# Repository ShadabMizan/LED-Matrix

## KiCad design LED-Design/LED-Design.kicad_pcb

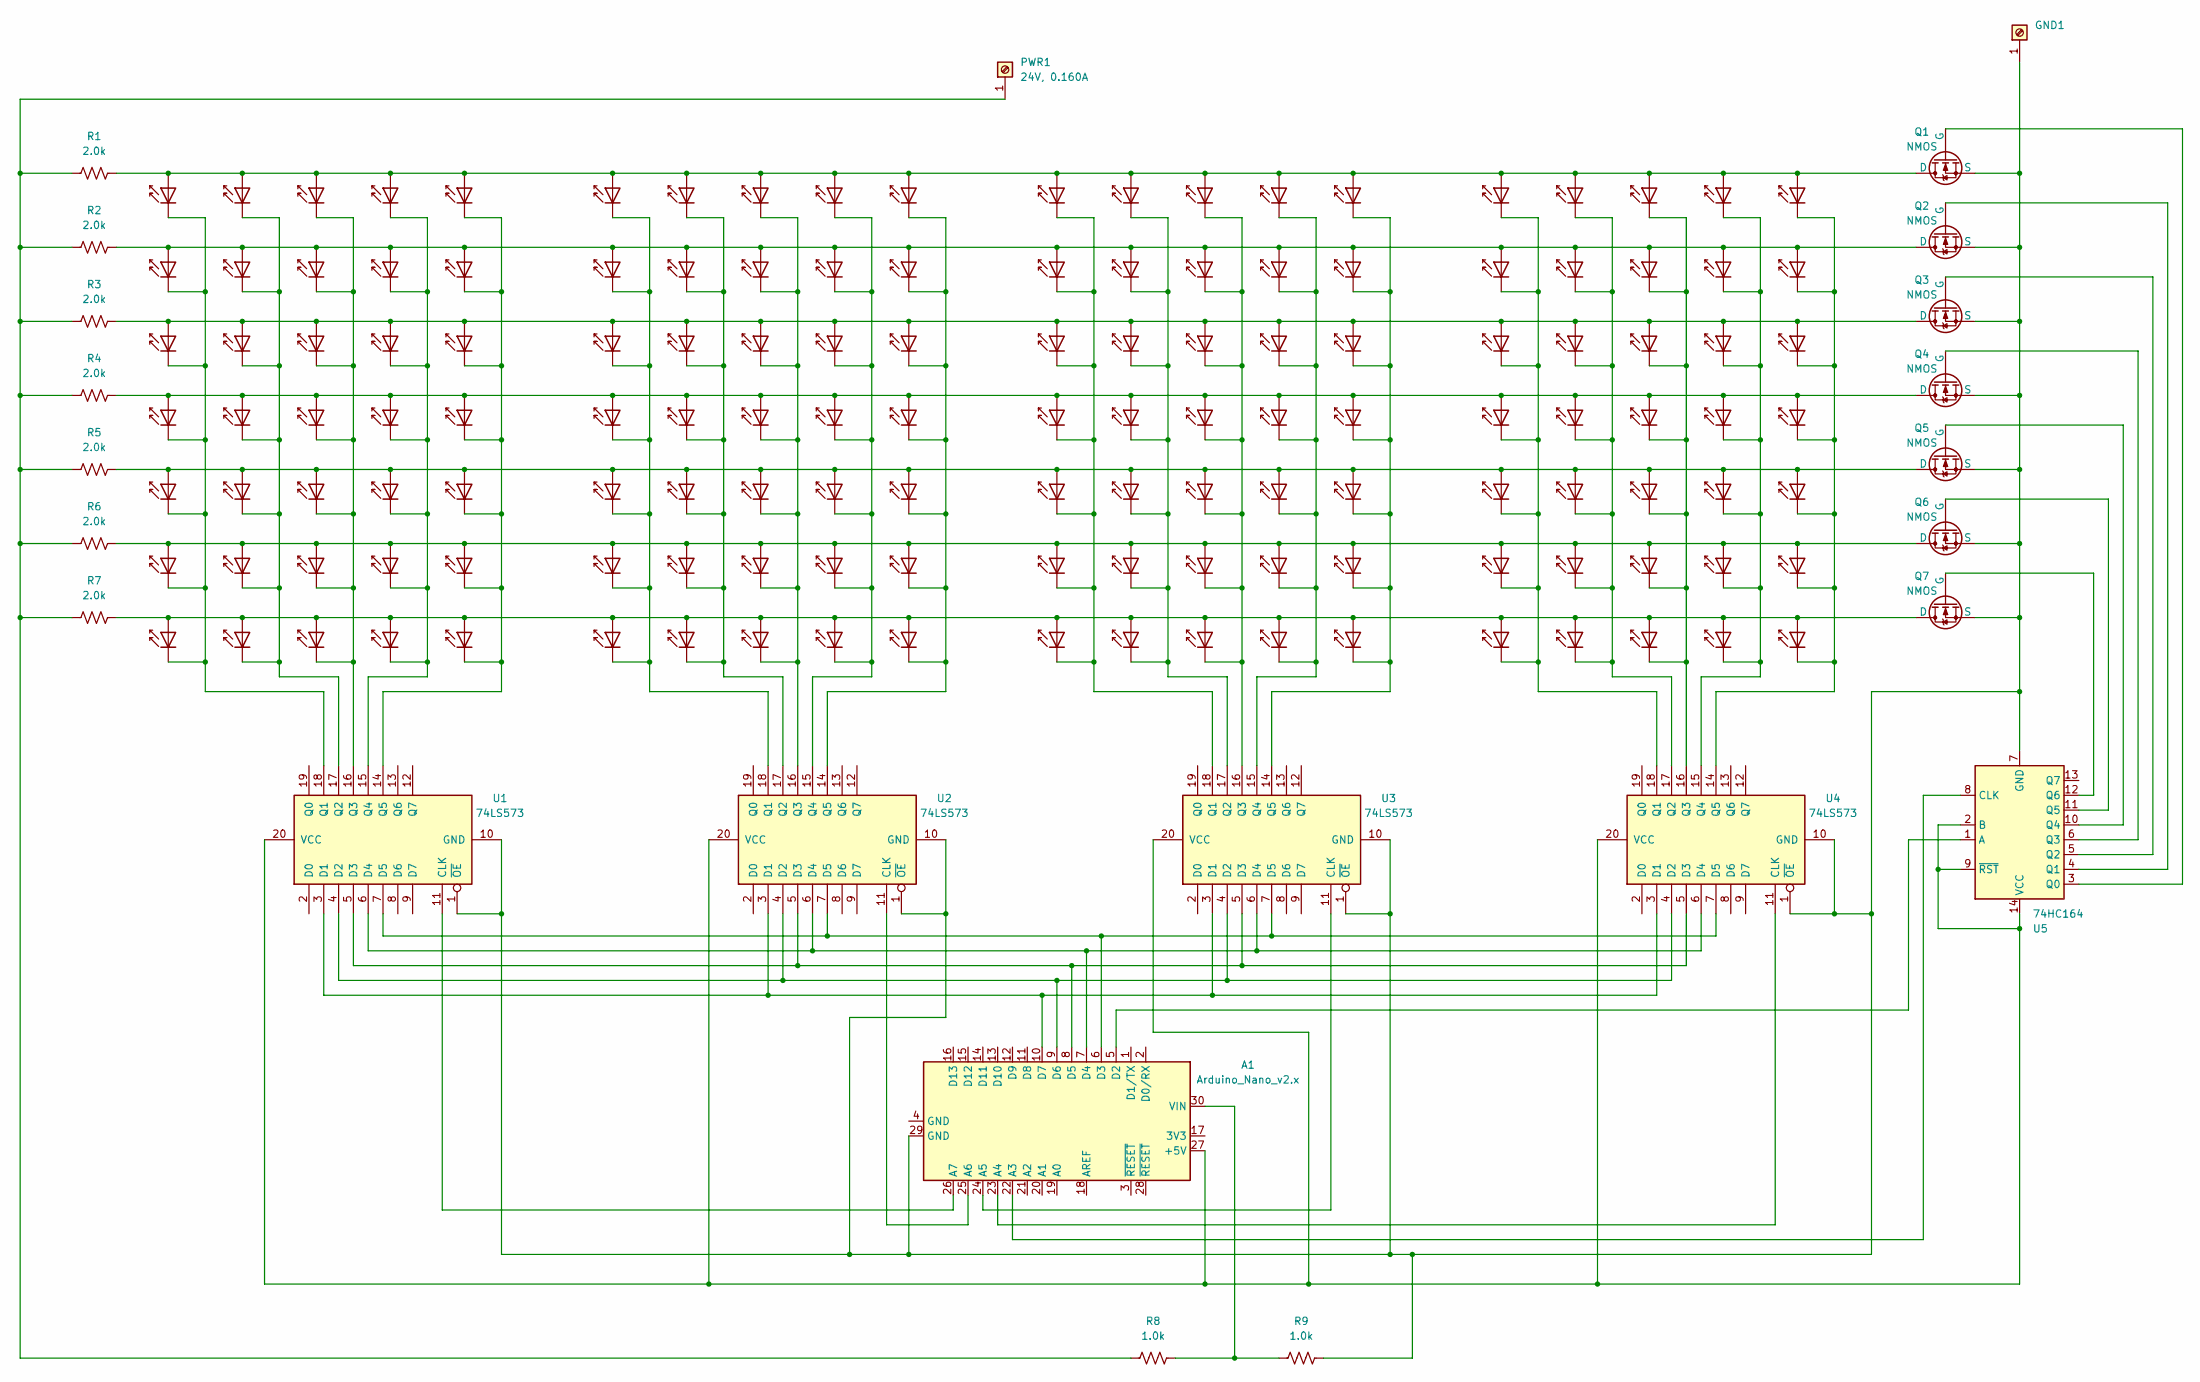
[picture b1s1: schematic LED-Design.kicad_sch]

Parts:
A1: Arduino_Nano_v2.x; Arduino_Nano
D1, D2, D3, D4, D5, D6, D7, D8, D9, D10, D11, D12, D13, D14, D15, D16, D17, D18, D19, D20, D21, D22, D23, D24, D25, D26, D27, D28, D29, D30, D31, D32, D33, D34, D35, D36, D37, D38, D39, D40, D41, D42, D43, D44, D45, D46, D47, D48, D49, D50, D51, D52, D53, D54, D55, D56, D57, D58, D59, D60, D61, D62, D63, D64, D65, D66, D67, D68, D69, D70, D71, D72, D73, D74, D75, D76, D77, D78, D79, D80, D81, D82, D83, D84, D85, D86, D87, D88, D89, D90, D91, D92, D93, D94, D95, D96, D97, D98, D99, D100, D101, D102, D103, D104, D105, D106, D107, D108, D109, D110, D111, D112, D113, D114, D115, D116, D117, D118, D119, D120, D121, D122, D123, D124, D125, D126, D127, D128, D129, D130, D131, D132, D133, D134, D135, D136, D137, D138, D139, D140: IR204A; LED_D3.0mm_IRBlack
GND1: TerminalBlock_MetzConnect_360271_1x01_Horizontal_ScrewM3.0_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
PWR1: 24V, 0.160A; TerminalBlock_MetzConnect_360271_1x01_Horizontal_ScrewM3.0_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
Q1, Q2, Q3, Q4, Q5, Q6, Q7: NMOS; TO-220-3_Vertical
R1, R2, R3, R4, R5, R6, R7: 2.0k; R_LDR_5.2x5.2mm_P3.5mm_Horizontal
R8, R9: 1.0k; R_LDR_5.2x5.2mm_P3.5mm_Horizontal
U1, U2, U3, U4: 74LS573; DIP-20_W7.62mm
U5: 74HC164; DIP-14_W7.62mm

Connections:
unnamed: A1.27 (+5V), U1.20 (VCC), U2.20 (VCC), U3.20 (VCC), U4.20 (VCC), U5.2 (B), U5.9 (~RST), U5.14 (VCC)
unnamed: A1.22 (A3), U5.8 (CLK)
unnamed: A1.23 (A4), U4.11 (CLK)
unnamed: A1.24 (A5), U3.11 (CLK)
unnamed: A1.25 (A6), U2.11 (CLK)
unnamed: A1.26 (A7), U1.11 (CLK)
unnamed: A1.5 (D2), U5.1 (A)
unnamed: A1.6 (D3), U1.7 (D5), U2.7 (D5), U3.7 (D5), U4.7 (D5)
unnamed: A1.7 (D4), U1.6 (D4), U2.6 (D4), U3.6 (D4), U4.6 (D4)
unnamed: A1.8 (D5), U1.5 (D3), U2.5 (D3), U3.5 (D3), U4.5 (D3)
unnamed: A1.9 (D6), U1.4 (D2), U2.4 (D2), U3.4 (D2), U4.4 (D2)
unnamed: A1.10 (D7), U1.3 (D1), U2.3 (D1), U3.3 (D1), U4.3 (D1)
unnamed: A1.30 (VIN), R8.2, R9.1
unnamed: D1.2 (A), D8.2 (A), D15.2 (A), D22.2 (A), D29.2 (A), D36.2 (A), D43.2 (A), D50.2 (A), D57.2 (A), D64.2 (A), D71.2 (A), D78.2 (A), D85.2 (A), D92.2 (A), D99.2 (A), D106.2 (A), D113.2 (A), D120.2 (A), D127.2 (A), D134.2 (A), Q1.2 (D), R1.2
unnamed: D1.1 (K), D2.1 (K), D3.1 (K), D4.1 (K), D5.1 (K), D6.1 (K), D7.1 (K), U1.18 (Q1)
unnamed: D3.2 (A), D10.2 (A), D17.2 (A), D24.2 (A), D31.2 (A), D38.2 (A), D45.2 (A), D52.2 (A), D59.2 (A), D66.2 (A), D73.2 (A), D80.2 (A), D87.2 (A), D94.2 (A), D101.2 (A), D108.2 (A), D115.2 (A), D122.2 (A), D129.2 (A), D136.2 (A), Q3.2 (D), R3.2
unnamed: D8.1 (K), D9.1 (K), D10.1 (K), D11.1 (K), D12.1 (K), D13.1 (K), D14.1 (K), U1.17 (Q2)
unnamed: D15.1 (K), D16.1 (K), D17.1 (K), D18.1 (K), D19.1 (K), D20.1 (K), D21.1 (K), U1.16 (Q3)
unnamed: D22.1 (K), D23.1 (K), D24.1 (K), D25.1 (K), D26.1 (K), D27.1 (K), D28.1 (K), U1.15 (Q4)
unnamed: D29.1 (K), D30.1 (K), D31.1 (K), D32.1 (K), D33.1 (K), D34.1 (K), D35.1 (K), U1.14 (Q5)
unnamed: D36.1 (K), D37.1 (K), D38.1 (K), D39.1 (K), D40.1 (K), D41.1 (K), D42.1 (K), U2.18 (Q1)
unnamed: D43.1 (K), D44.1 (K), D45.1 (K), D46.1 (K), D47.1 (K), D48.1 (K), D49.1 (K), U2.17 (Q2)
unnamed: D50.1 (K), D51.1 (K), D52.1 (K), D53.1 (K), D54.1 (K), D55.1 (K), D56.1 (K), U2.16 (Q3)
unnamed: D57.1 (K), D58.1 (K), D59.1 (K), D60.1 (K), D61.1 (K), D62.1 (K), D63.1 (K), U2.15 (Q4)
unnamed: D64.1 (K), D65.1 (K), D66.1 (K), D67.1 (K), D68.1 (K), D69.1 (K), D70.1 (K), U2.14 (Q5)
unnamed: D71.1 (K), D72.1 (K), D73.1 (K), D74.1 (K), D75.1 (K), D76.1 (K), D77.1 (K), U3.18 (Q1)
unnamed: D78.1 (K), D79.1 (K), D80.1 (K), D81.1 (K), D82.1 (K), D83.1 (K), D84.1 (K), U3.17 (Q2)
unnamed: D85.1 (K), D86.1 (K), D87.1 (K), D88.1 (K), D89.1 (K), D90.1 (K), D91.1 (K), U3.16 (Q3)
unnamed: D92.1 (K), D93.1 (K), D94.1 (K), D95.1 (K), D96.1 (K), D97.1 (K), D98.1 (K), U3.15 (Q4)
unnamed: D2.2 (A), D9.2 (A), D16.2 (A), D23.2 (A), D30.2 (A), D37.2 (A), D44.2 (A), D51.2 (A), D58.2 (A), D65.2 (A), D72.2 (A), D79.2 (A), D86.2 (A), D93.2 (A), D100.2 (A), D107.2 (A), D114.2 (A), D121.2 (A), D128.2 (A), D135.2 (A), Q2.2 (D), R2.2
unnamed: D99.1 (K), D100.1 (K), D101.1 (K), D102.1 (K), D103.1 (K), D104.1 (K), D105.1 (K), U3.14 (Q5)
unnamed: D4.2 (A), D11.2 (A), D18.2 (A), D25.2 (A), D32.2 (A), D39.2 (A), D46.2 (A), D53.2 (A), D60.2 (A), D67.2 (A), D74.2 (A), D81.2 (A), D88.2 (A), D95.2 (A), D102.2 (A), D109.2 (A), D116.2 (A), D123.2 (A), D130.2 (A), D137.2 (A), Q4.2 (D), R4.2
unnamed: D5.2 (A), D12.2 (A), D19.2 (A), D26.2 (A), D33.2 (A), D40.2 (A), D47.2 (A), D54.2 (A), D61.2 (A), D68.2 (A), D75.2 (A), D82.2 (A), D89.2 (A), D96.2 (A), D103.2 (A), D110.2 (A), D117.2 (A), D124.2 (A), D131.2 (A), D138.2 (A), Q5.2 (D), R5.2
unnamed: D6.2 (A), D13.2 (A), D20.2 (A), D27.2 (A), D34.2 (A), D41.2 (A), D48.2 (A), D55.2 (A), D62.2 (A), D69.2 (A), D76.2 (A), D83.2 (A), D90.2 (A), D97.2 (A), D104.2 (A), D111.2 (A), D118.2 (A), D125.2 (A), D132.2 (A), D139.2 (A), Q6.2 (D), R6.2
unnamed: D7.2 (A), D14.2 (A), D21.2 (A), D28.2 (A), D35.2 (A), D42.2 (A), D49.2 (A), D56.2 (A), D63.2 (A), D70.2 (A), D77.2 (A), D84.2 (A), D91.2 (A), D98.2 (A), D105.2 (A), D112.2 (A), D119.2 (A), D126.2 (A), D133.2 (A), D140.2 (A), Q7.2 (D), R7.2
unnamed: D106.1 (K), D107.1 (K), D108.1 (K), D109.1 (K), D110.1 (K), D111.1 (K), D112.1 (K), U4.18 (Q1)
unnamed: D113.1 (K), D114.1 (K), D115.1 (K), D116.1 (K), D117.1 (K), D118.1 (K), D119.1 (K), U4.17 (Q2)
unnamed: D120.1 (K), D121.1 (K), D122.1 (K), D123.1 (K), D124.1 (K), D125.1 (K), D126.1 (K), U4.16 (Q3)
unnamed: D127.1 (K), D128.1 (K), D129.1 (K), D130.1 (K), D131.1 (K), D132.1 (K), D133.1 (K), U4.15 (Q4)
unnamed: D134.1 (K), D135.1 (K), D136.1 (K), D137.1 (K), D138.1 (K), D139.1 (K), D140.1 (K), U4.14 (Q5)
unnamed: A1.29 (GND), GND1.1, Q1.3 (S), Q2.3 (S), Q3.3 (S), Q4.3 (S), Q5.3 (S), Q6.3 (S), Q7.3 (S), R9.2, U1.1 (~OE), U1.10 (GND), U2.1 (~OE), U2.10 (GND), U3.1 (~OE), U3.10 (GND), U4.1 (~OE), U4.10 (GND), U5.7 (GND)
unnamed: PWR1.1, R1.1, R2.1, R3.1, R4.1, R5.1, R6.1, R7.1, R8.1
unnamed: Q1.1 (G), U5.3 (Q0)
unnamed: Q2.1 (G), U5.4 (Q1)
unnamed: Q3.1 (G), U5.5 (Q2)
unnamed: Q4.1 (G), U5.6 (Q3)
unnamed: Q5.1 (G), U5.10 (Q4)
unnamed: Q6.1 (G), U5.11 (Q5)
unnamed: Q7.1 (G), U5.12 (Q6)

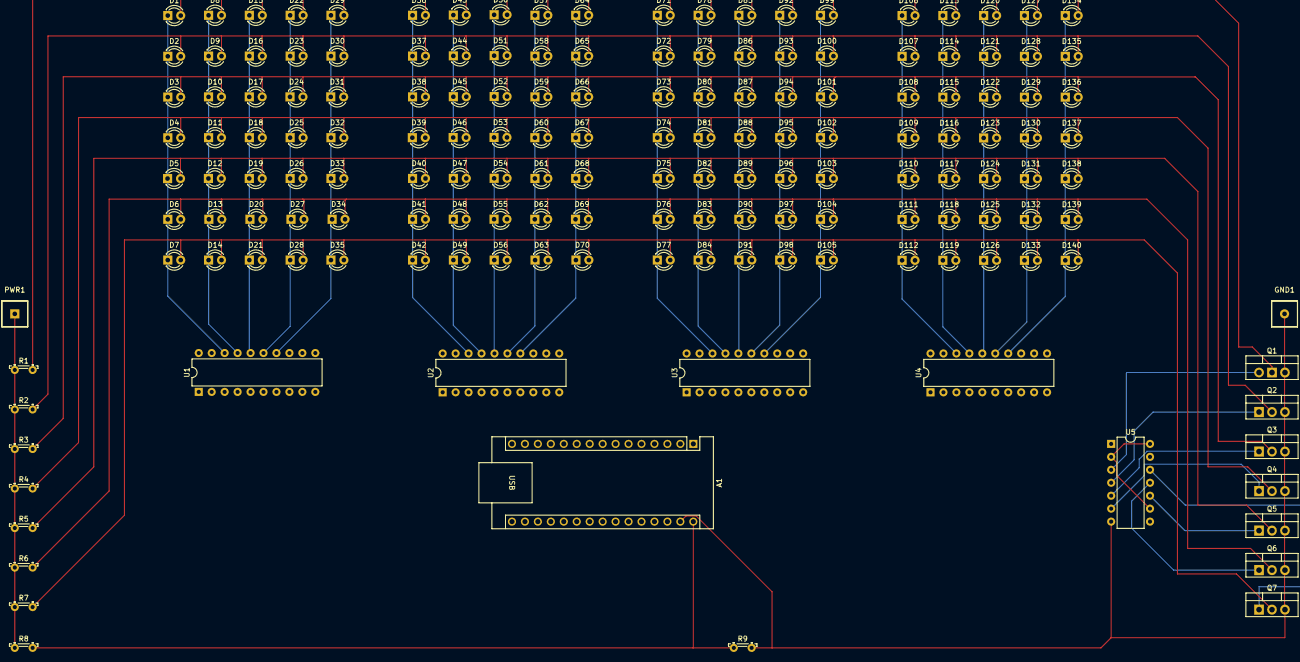
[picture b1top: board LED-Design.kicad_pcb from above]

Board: 2 copper layers, 164 parts (0 on the bottom side), 49 nets.

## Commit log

2024-03-25 Merged from Voltaire's branch
2024-03-25 Added a Voltage divider
2024-03-25 Added all components to the schematic and linked them to their footprints
2024-03-26 Used the distribute function in PCB Design to correctly align all the LEDs in their matrix. Used an 8mm gap between all LEDs
2024-03-27 Fixed the assignment of the MOSFET footprints to be GDS.
2024-03-27 Added footprints for ground and power
2024-03-28 Added the majority of traces
